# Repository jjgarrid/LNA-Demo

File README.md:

# LNA-Demo
LNA HW project demo

This is a small project to demostrate the feasibility of design, build and test an integrated circuit. 

This Low Noise Amplifier has been built and tested.

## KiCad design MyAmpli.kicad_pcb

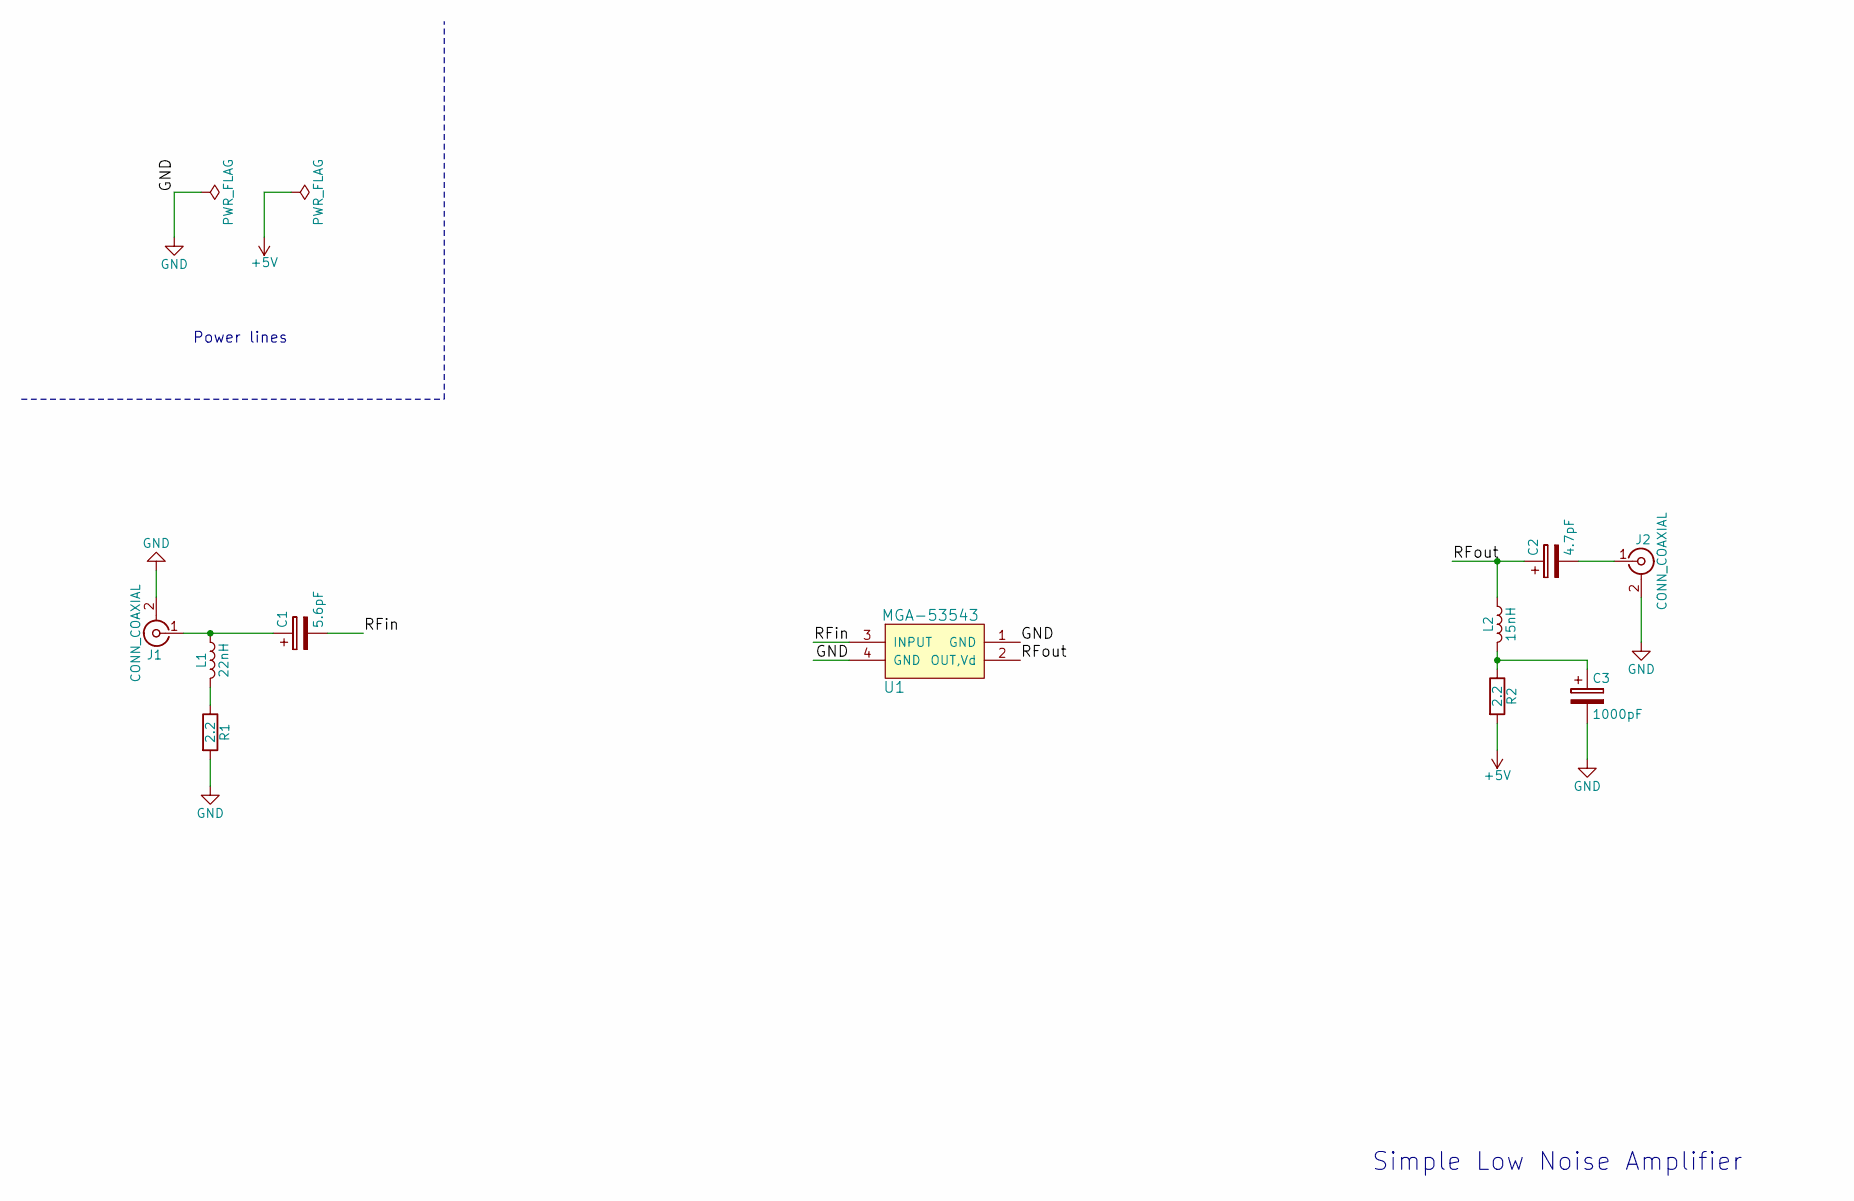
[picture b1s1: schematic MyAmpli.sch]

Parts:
C1: 5.6pF; C_0603_HandSoldering
C2: 4.7pF; C_0603_HandSoldering
C3: 1000pF; C_0603_HandSoldering
J1, J2: CONN_COAXIAL; SMA_THT_Jack_Straight
L1: 22nH; L_0603_HandSoldering
L2: 15nH; L_0603_HandSoldering
R1, R2: 2.2; R_0603_HandSoldering
U1: MGA-53543; SOT-343_SC-70-4_Handsoldering

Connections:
+5V: R2.2
/RFin: C1.2, U1.3 (INPUT)
/RFout: C2.1, L2.1, U1.2 (OUT,Vd)
GND: C3.2, J1.2 (Ext), J2.2 (Ext), R1.2, U1.1 (GND), U1.4 (GND)
unnamed: C1.1, J1.1 (In), L1.1
unnamed: C2.2, J2.1 (In)
unnamed: C3.1, L2.2, R2.1
unnamed: L1.2, R1.1

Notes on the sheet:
Power lines
Simple Low Noise Amplifier

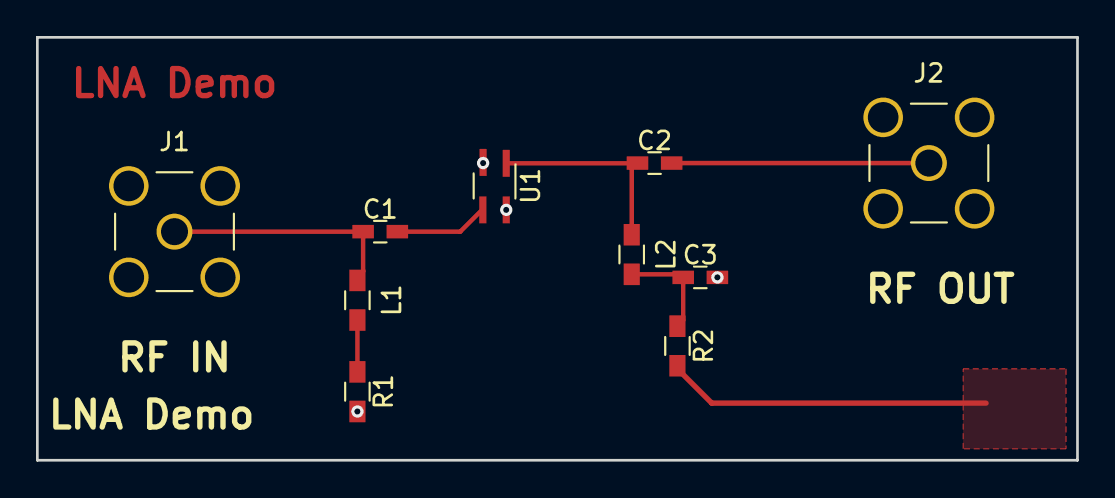
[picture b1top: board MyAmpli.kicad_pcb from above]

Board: 2 copper layers, 57.8 x 23.5 mm, 10 parts (0 on the bottom side), 7 nets.

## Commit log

2018-03-14 Added a preliminary description
2018-03-14 added .gitignore file with the files that shouldn´t be uploaded
2018-03-14 Delete #photos-1.dropbox.com.url
    Not relevant
